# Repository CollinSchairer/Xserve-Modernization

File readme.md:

Making Apple's beautiful but whacky servers of old useable in 2023.

This project aims to adapt modern ATX computer hardware into the 1U Xserve chassis while maintaining as much of the original design and hardware as possible.
As I work through this project, less and less of this original hardware seems to be useable, but I'm trying my best.

The main components of this modification are a revised front panel I/O and indication board, hard drive caddy modifications, a revised and modernized 
SATA (Maybe SAS?) backplane, and a revised back panel to fit an ATX motherboard I/O cutout and Flex ATX power supply.
# Xserve-Modernization

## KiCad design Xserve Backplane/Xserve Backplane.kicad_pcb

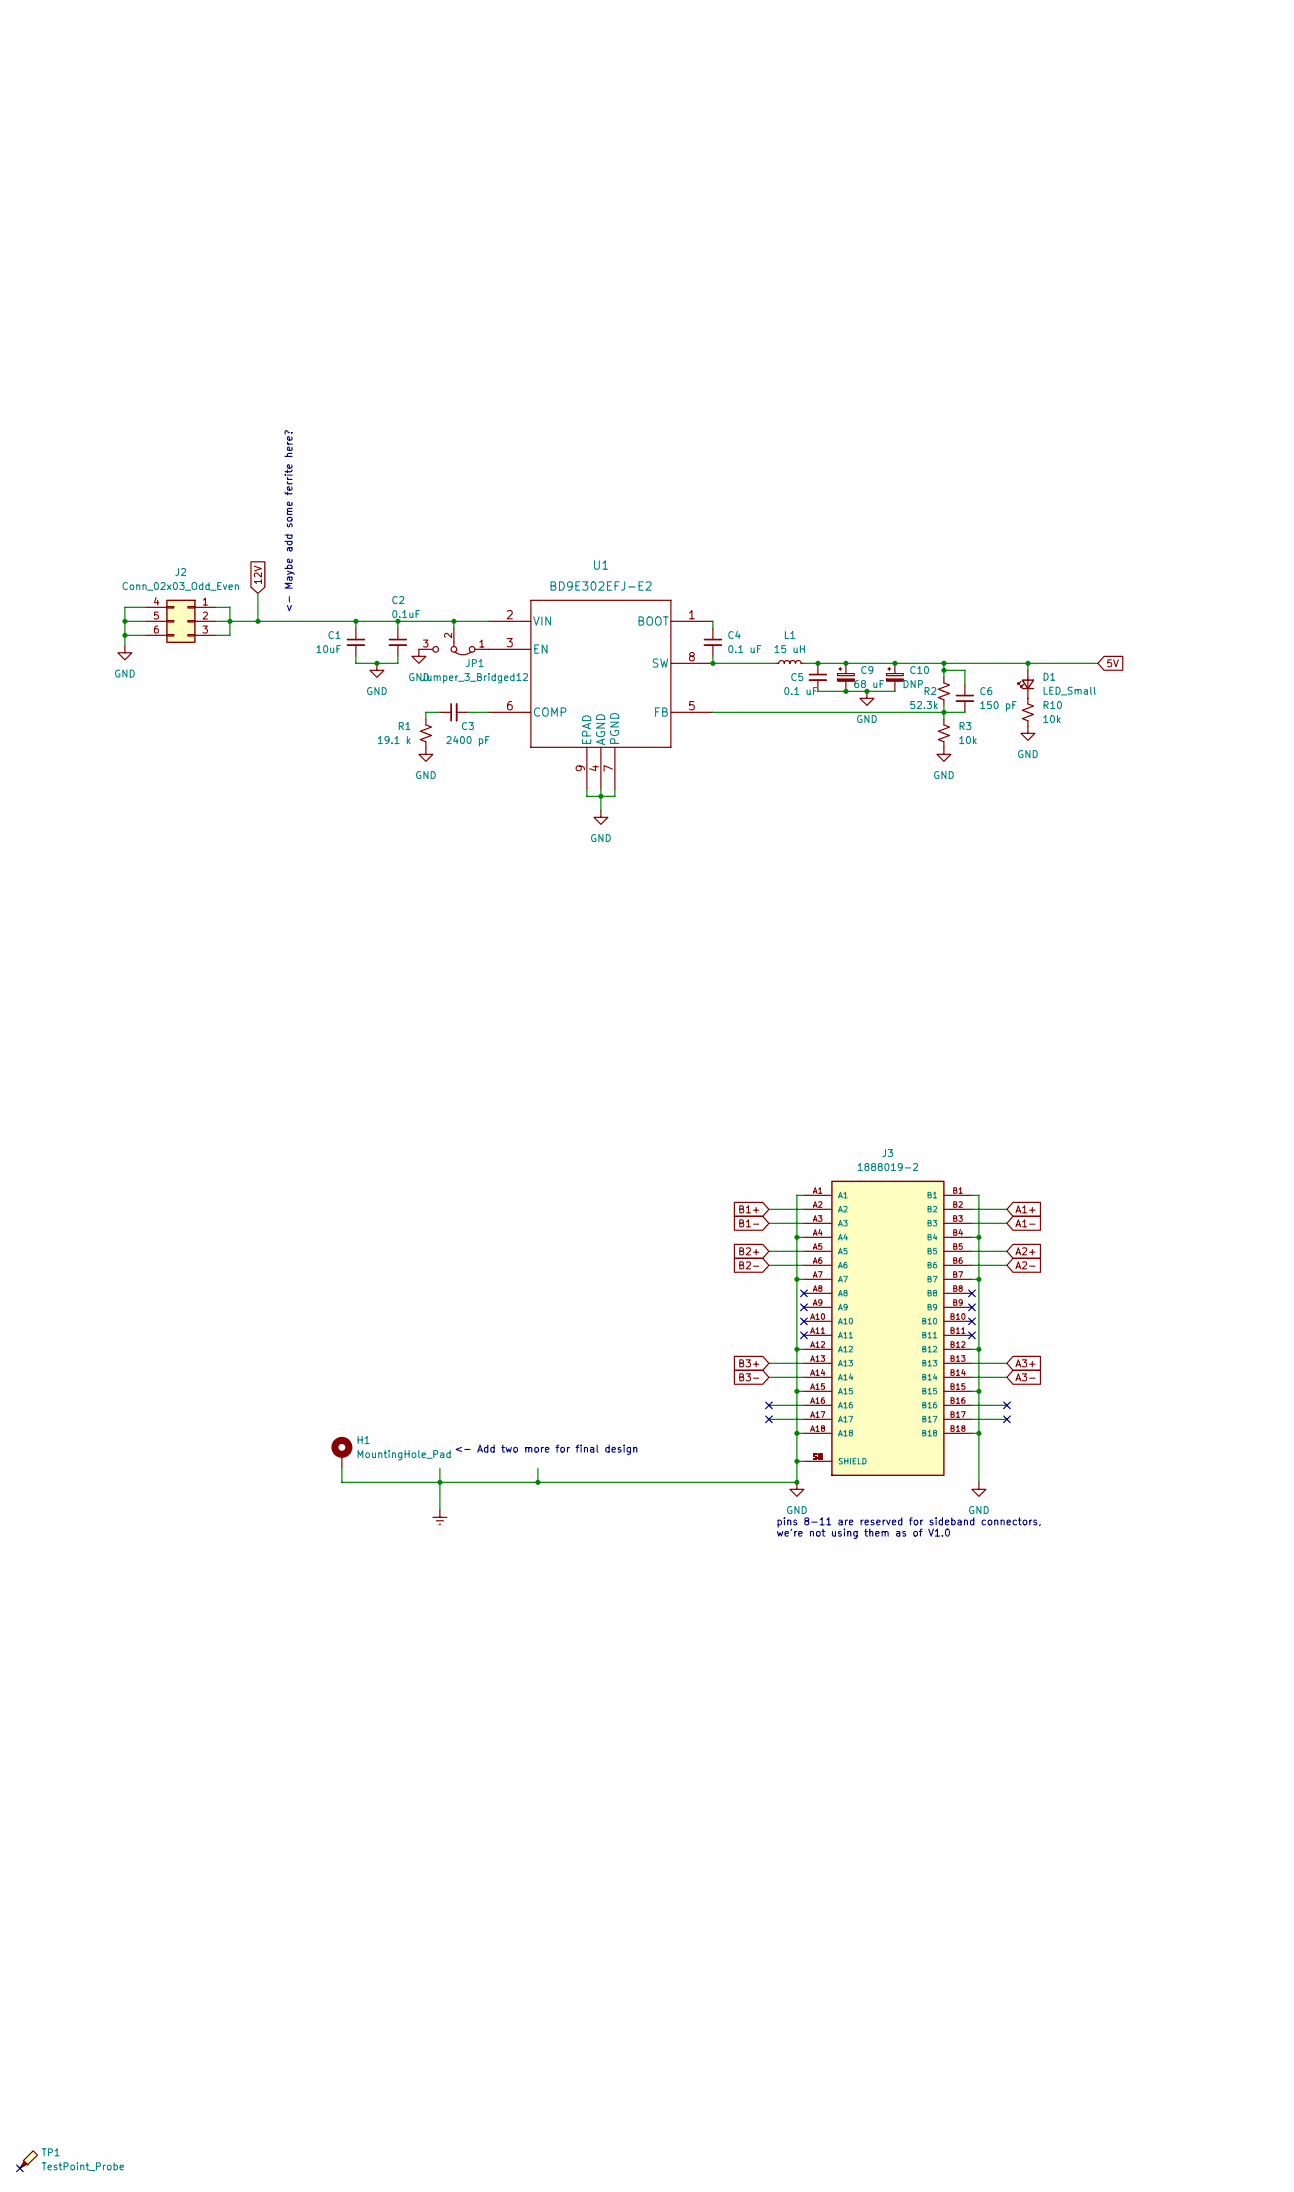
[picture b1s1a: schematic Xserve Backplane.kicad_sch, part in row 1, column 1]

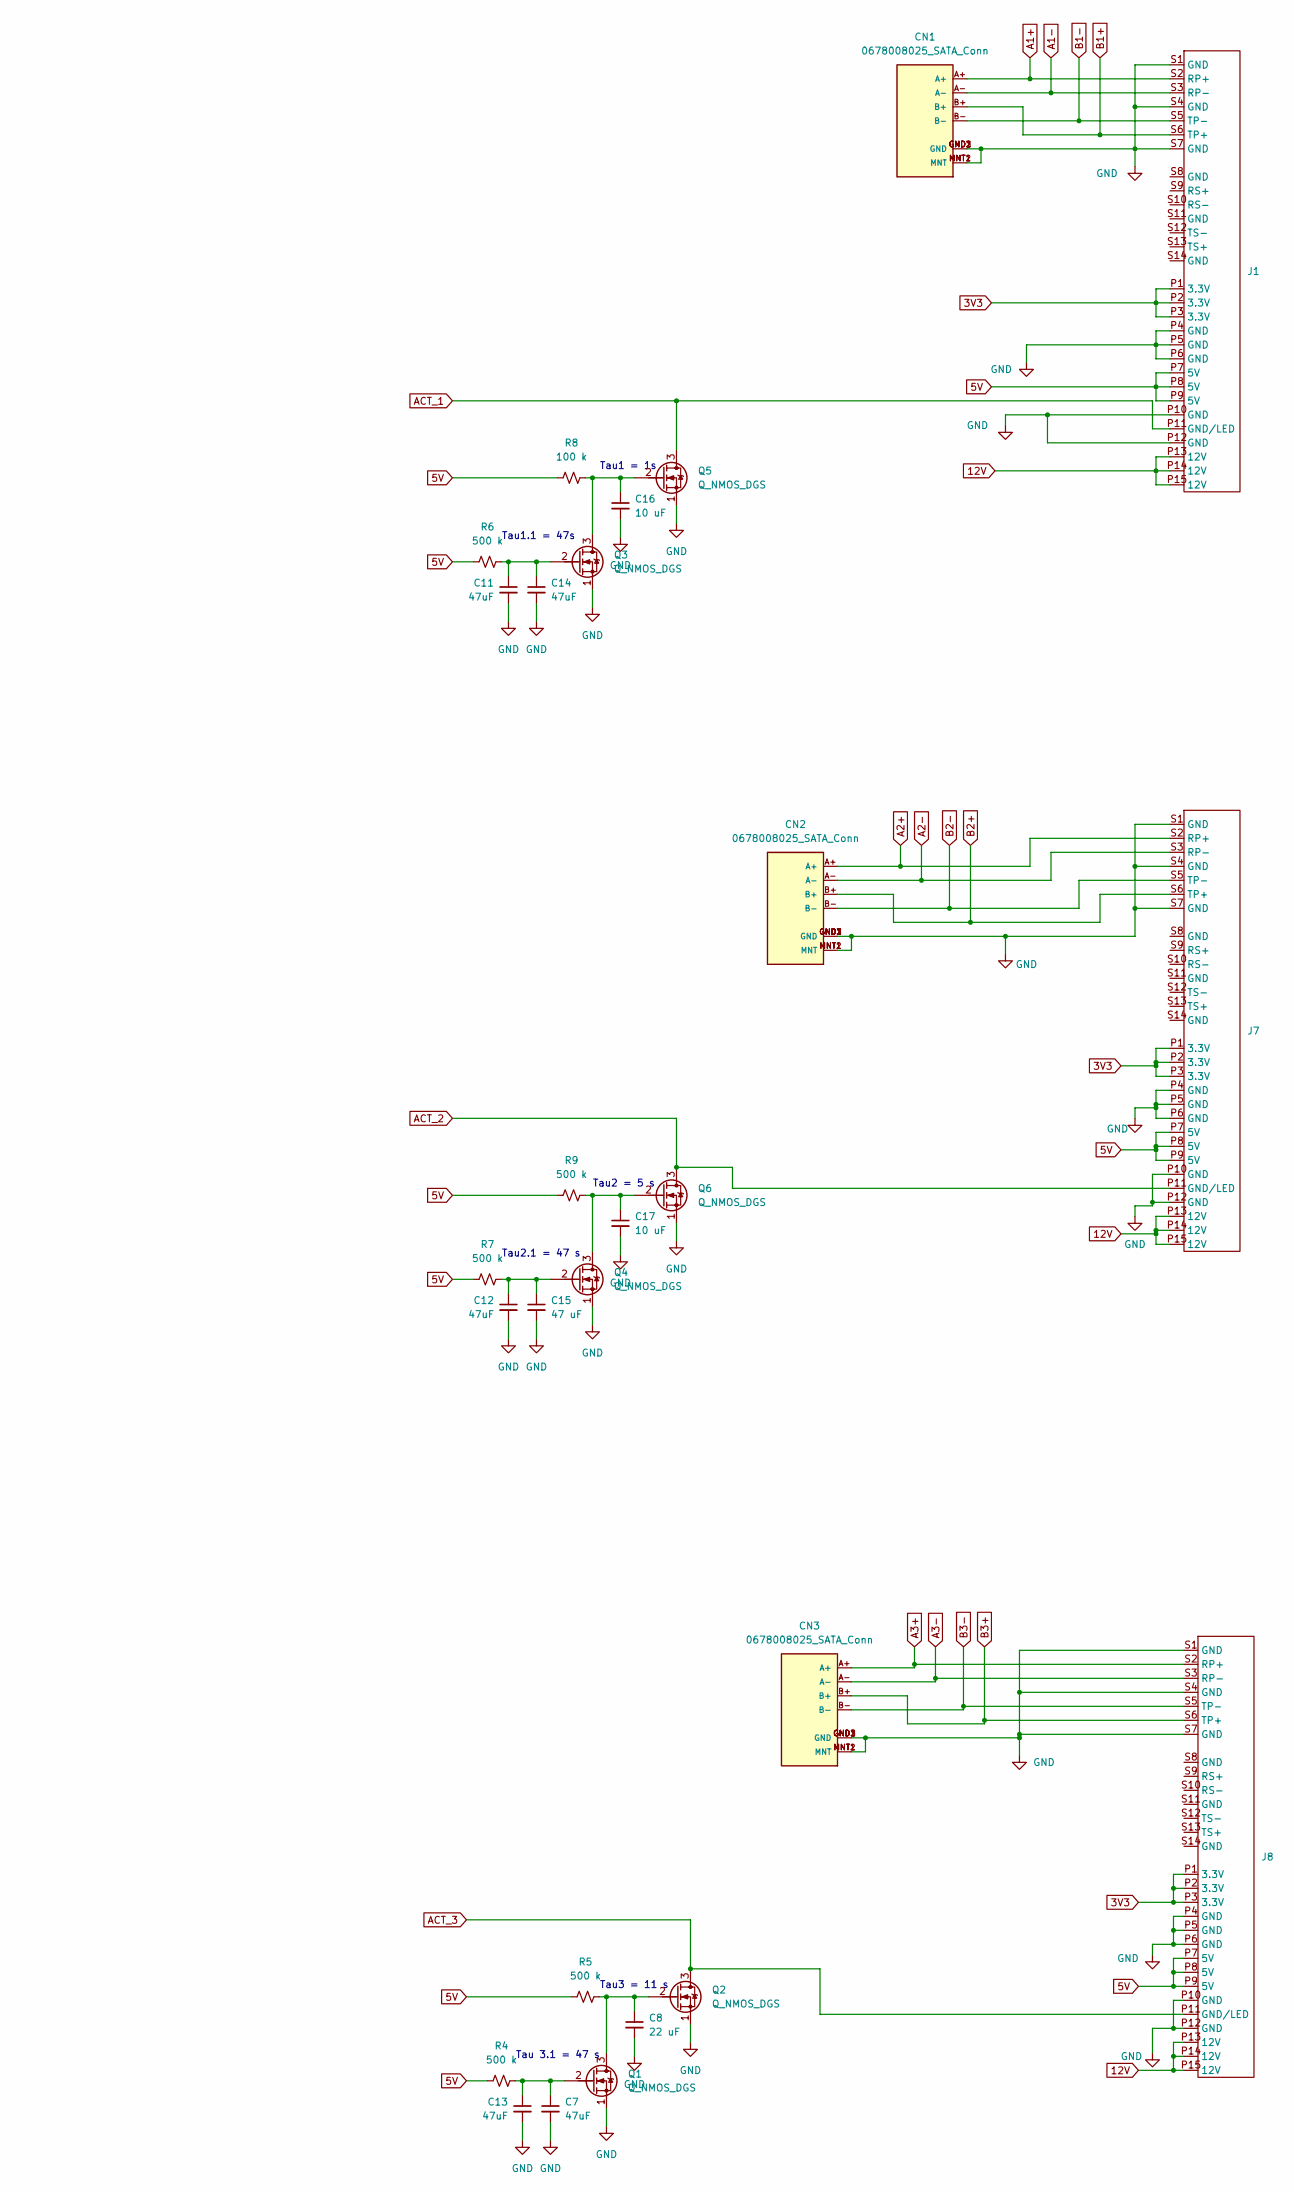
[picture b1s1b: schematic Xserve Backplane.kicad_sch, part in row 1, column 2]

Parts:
C1: 10uF; C_0603_1608Metric_Pad1.08x0.95mm_HandSolder
C2: 0.1uF; C_0603_1608Metric_Pad1.08x0.95mm_HandSolder
C3: 2400 pF; C_0603_1608Metric_Pad1.08x0.95mm_HandSolder
C4, C5: 0.1 uF; C_0603_1608Metric_Pad1.08x0.95mm_HandSolder
C6: 150 pF; C_0603_1608Metric_Pad1.08x0.95mm_HandSolder
C7, C11, C12, C13, C14: 47uF; C_1210_3225Metric_Pad1.33x2.70mm_HandSolder
C8: 22 uF; C_0603_1608Metric_Pad1.08x0.95mm_HandSolder
C9: 68 uF; CP_EIA-7343-15_Kemet-W_Pad2.25x2.55mm_HandSolder
C10: DNP; CP_EIA-7343-15_Kemet-W_Pad2.25x2.55mm_HandSolder
C15: 47 uF; C_1210_3225Metric_Pad1.33x2.70mm_HandSolder
C16, C17: 10 uF; C_0603_1608Metric_Pad1.08x0.95mm_HandSolder
CN1, CN2, CN3: 0678008025_SATA_Conn
D1: LED_Small; LED_0805_2012Metric_Pad1.15x1.40mm_HandSolder
H1: MountingHole_Pad; Slide Mount Hole
J1, J7, J8: 10124274-001TRLF
J2: Conn_02x03_Odd_Even; 6_pin_PCI_PWR
J3: 1888019-2; TE_1888019-2
JP1: Jumper_3_Bridged12; SolderJumper-3_P1.3mm_Bridged2Bar12_Pad1.0x1.5mm_NumberLabe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
L1: 15 uH; L_12x12mm_H8mm
Q1, Q2, Q3, Q4, Q5, Q6: Q_NMOS_DGS; SOT-23
R1: 19.1 k; R_0603_1608Metric_Pad0.98x0.95mm_HandSolder
R2: 52.3k; R_0603_1608Metric_Pad0.98x0.95mm_HandSolder
R3, R10: 10k; R_0603_1608Metric_Pad0.98x0.95mm_HandSolder
R4, R5, R6, R7, R9: 500 k; R_0603_1608Metric_Pad0.98x0.95mm_HandSolder
R8: 100 k; R_0603_1608Metric_Pad0.98x0.95mm_HandSolder
TP1: TestPoint_Probe; TheColonelCu
U1: BD9E302EFJ-E2; Texas_HTSOP-8-1EP_3.9x4.9mm_P1.27mm_EP2.95x4.9mm_Mask2.4x3.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

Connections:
3V3: J1.P1 (3.3V), J1.P2 (3.3V), J1.P3 (3.3V), J7.P1 (3.3V), J7.P2 (3.3V), J7.P3 (3.3V), J8.P1 (3.3V), J8.P2 (3.3V), J8.P3 (3.3V)
5V: C5.1, C6.1, C9.1, C10.1, D1.2 (A), J1.P7 (5V), J1.P8 (5V), J1.P9 (5V), J7.P7 (5V), J7.P8 (5V), J7.P9 (5V), J8.P7 (5V), J8.P8 (5V), J8.P9 (5V), L1.2, R2.1, R4.1, R5.1, R6.1, R7.1, R8.1, R9.1
12V: C1.1, C2.1, J1.P13 (12V), J1.P14 (12V), J1.P15 (12V), J2.1, J2.2, J2.3, J7.P13 (12V), J7.P14 (12V), J7.P15 (12V), J8.P13 (12V), J8.P14 (12V), J8.P15 (12V), JP1.2 (C), U1.2 (VIN)
A1+: CN1.A+, J1.S2 (RP+), J3.B2
A1-: CN1.A-, J1.S3 (RP-), J3.B3
A2+: CN2.A+, J3.B5, J7.S2 (RP+)
A2-: CN2.A-, J3.B6, J7.S3 (RP-)
A3+: CN3.A+, J3.B13, J8.S2 (RP+)
A3-: CN3.A-, J3.B14, J8.S3 (RP-)
ACT_1: J1.P11 (GND/LED), Q5.3 (D)
ACT_2: J7.P11 (GND/LED), Q6.3 (D)
ACT_3: J8.P11 (GND/LED), Q2.3 (D)
B1+: CN1.B+, J1.S6 (TP+), J3.A2
B1-: CN1.B-, J1.S5 (TP-), J3.A3
B2+: CN2.B+, J3.A5, J7.S6 (TP+)
B2-: CN2.B-, J3.A6, J7.S5 (TP-)
B3+: CN3.B+, J3.A13, J8.S6 (TP+)
B3-: CN3.B-, J3.A14, J8.S5 (TP-)
Earth: C1.2, C2.2, C5.2, C7.2, C8.2, C9.2, C10.2, C11.2, C12.2, C13.2, C14.2, C15.2, C16.2, C17.2, CN1.GND1 (GND), CN1.GND2 (GND), CN1.GND3 (GND), CN1.MNT1 (MNT), CN1.MNT2 (MNT), CN2.GND1 (GND), CN2.GND2 (GND), CN2.GND3 (GND), CN2.MNT1 (MNT), CN2.MNT2 (MNT), CN3.GND1 (GND), CN3.GND2 (GND), CN3.GND3 (GND), CN3.MNT1 (MNT), CN3.MNT2 (MNT), H1.1, J1.P4 (GND), J1.P5 (GND), J1.P6 (GND), J1.P10 (GND), J1.P12 (GND), J1.S1 (GND), J1.S4 (GND), J1.S7 (GND), J2.4, J2.5, J2.6, J3.A1, J3.A4, J3.A7, J3.A12, J3.A15, J3.A18, J3.B1, J3.B4, J3.B7, J3.B12, J3.B15, J3.B18, J3.S1 (SHIELD), J3.S2 (SHIELD), J3.S3 (SHIELD), J3.S4 (SHIELD), J3.S5 (SHIELD), J3.S6 (SHIELD), J7.P4 (GND), J7.P5 (GND), J7.P6 (GND), J7.P10 (GND), J7.P12 (GND), J7.S1 (GND), J7.S4 (GND), J7.S7 (GND), J8.P4 (GND), J8.P5 (GND), J8.P6 (GND), J8.P10 (GND), J8.P12 (GND), J8.S1 (GND), J8.S4 (GND), J8.S7 (GND), JP1.3 (B), Q1.1 (S), Q2.1 (S), Q3.1 (S), Q4.1 (S), Q5.1 (S), Q6.1 (S), R1.2, R3.2, R10.2, U1.4 (AGND), U1.7 (PGND), U1.9 (EPAD)
unnamed: C3.1, R1.1
unnamed: D1.1 (K), R10.1
unnamed: JP1.1 (A), U1.3 (EN)
unnamed: C8.1, Q1.3 (D), Q2.2 (G), R5.2
unnamed: C7.1, C13.1, Q1.2 (G), R4.2
unnamed: C16.1, Q3.3 (D), Q5.2 (G), R8.2
unnamed: C11.1, C14.1, Q3.2 (G), R6.2
unnamed: C17.1, Q4.3 (D), Q6.2 (G), R9.2
unnamed: C12.1, C15.1, Q4.2 (G), R7.2
unnamed: C4.1, U1.1 (BOOT)
unnamed: C3.2, U1.6 (COMP)
unnamed: C6.2, R2.2, R3.1, U1.5 (FB)
unnamed: C4.2, L1.1, U1.8 (SW)

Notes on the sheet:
Tau2.1 = 47 s
pins 8-11 are reserved for sideband connectors, we're not using them as of V1.0
<- Add two more for final design
Tau2 = 5 s
<- Maybe add some ferrite here?
Tau1 = 1s
Tau1.1 = 47s
Tau3 = 11 s
Tau 3.1 = 47 s

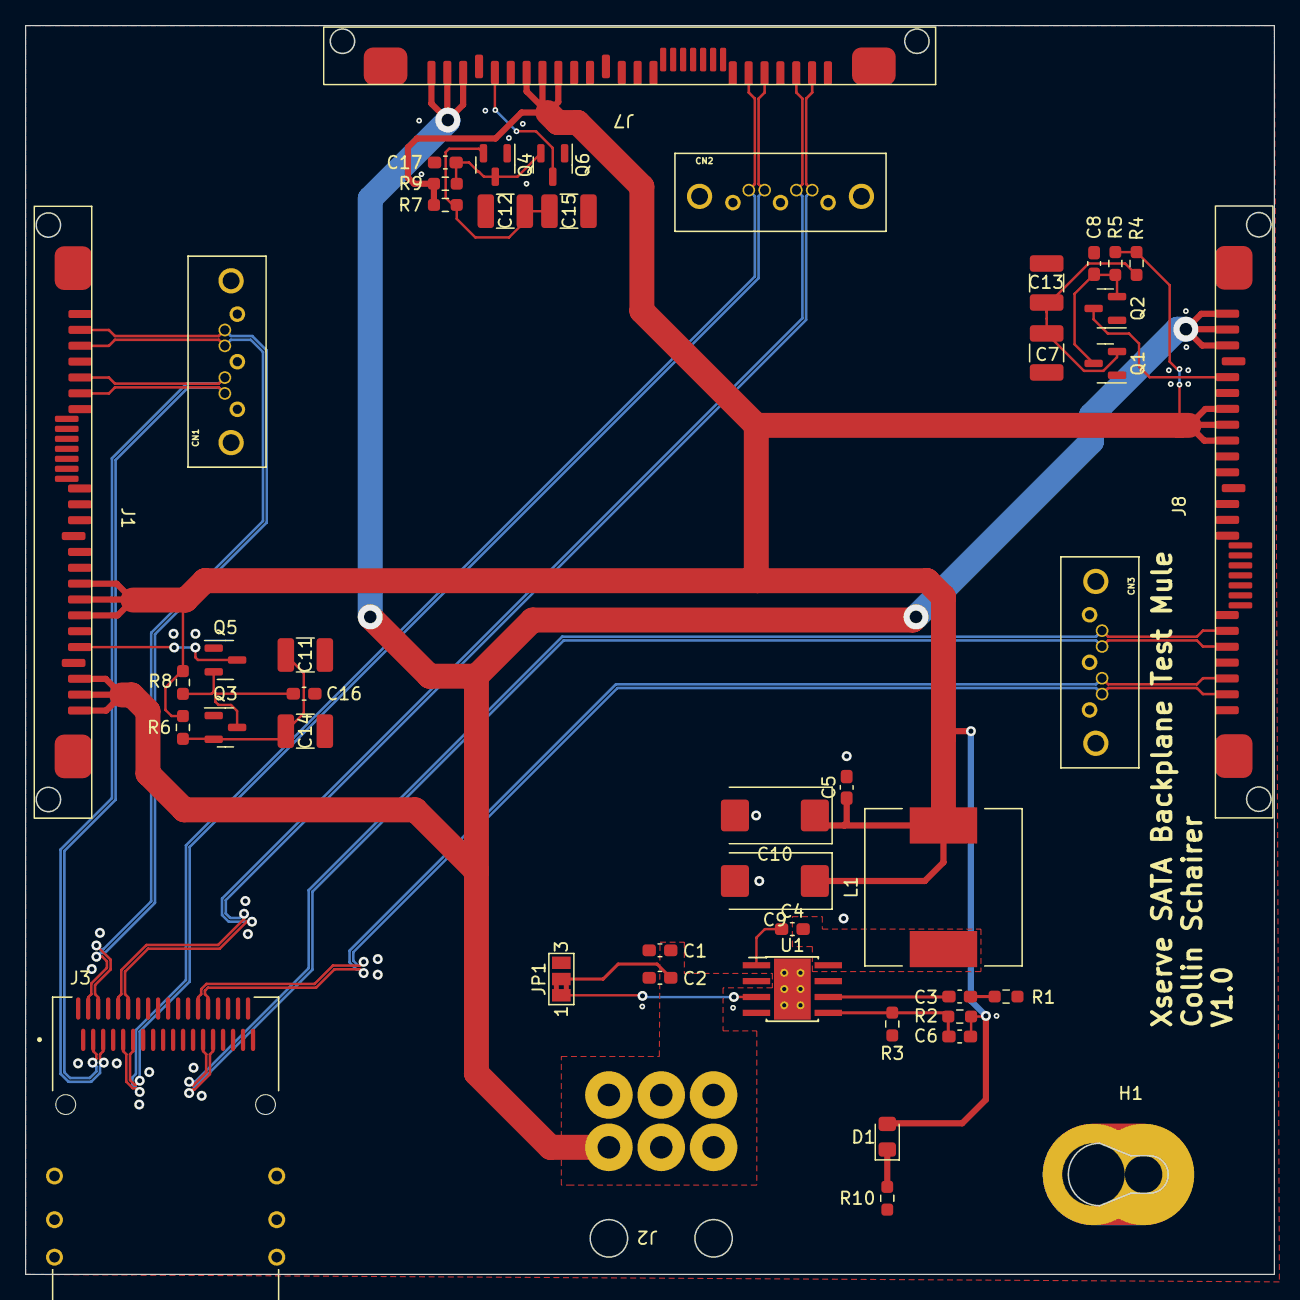
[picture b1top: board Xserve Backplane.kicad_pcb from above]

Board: 4 copper layers, 100.0 x 100.0 mm, 47 parts (0 on the bottom side), 32 nets.

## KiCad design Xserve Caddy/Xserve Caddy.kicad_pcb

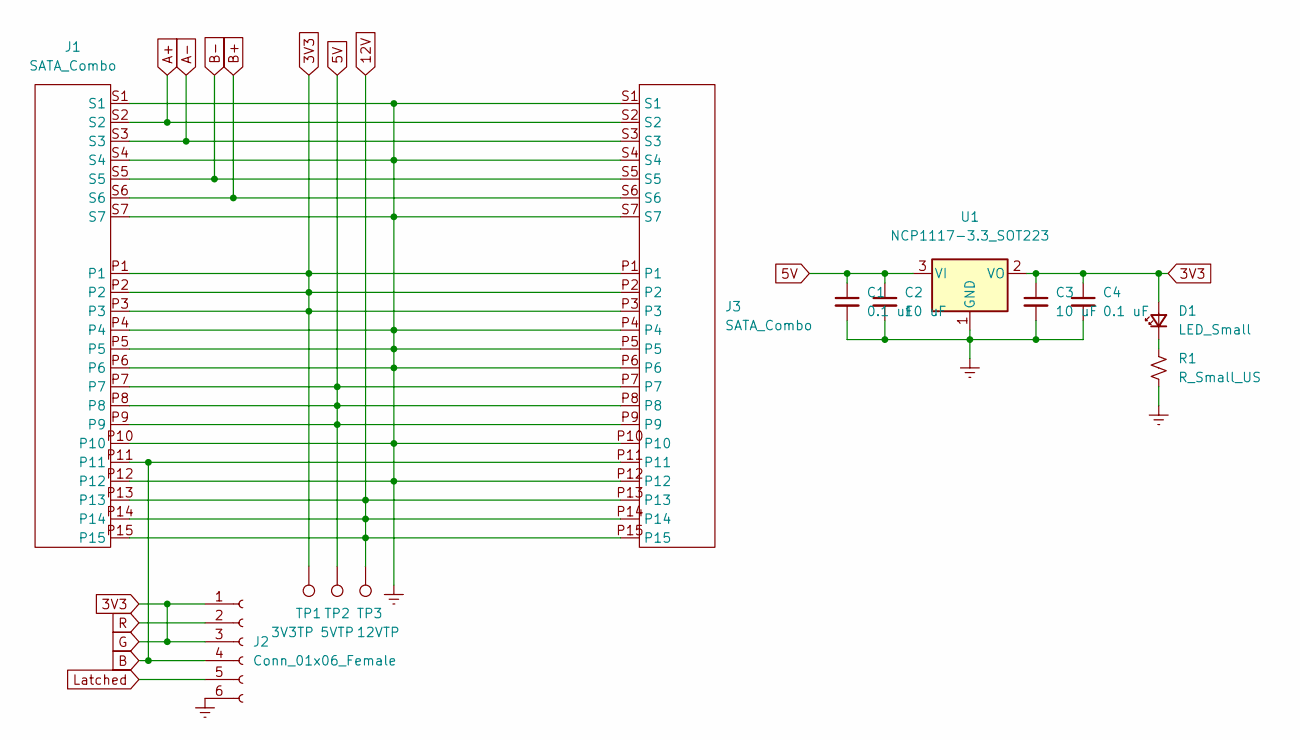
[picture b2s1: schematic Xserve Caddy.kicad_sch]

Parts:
C1, C4: 0.1 uF; C_0603_1608Metric_Pad1.08x0.95mm_HandSolder
C2, C3: 10 uF; C_0603_1608Metric_Pad1.08x0.95mm_HandSolder
D1: LED_Small; LED_0805_2012Metric_Pad1.15x1.40mm_HandSolder
J1, J3: SATA_Combo; 5622-2103-ML
J2: Conn_01x06_Female; Molex_PicoBlade_53048-0610_1x06_P1.25mm_Horizontal
R1: R_Small_US; R_0603_1608Metric_Pad0.98x0.95mm_HandSolder
TP1: 3V3TP; TestPoint_Pad_D2.0mm
TP2: 5VTP; TestPoint_Pad_D2.0mm
TP3: 12VTP; TestPoint_Pad_D2.0mm
U1: NCP1117-3.3_SOT223; SOT-223-3_TabPin2

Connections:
3V3: C3.1, C4.1, D1.2 (A), J1.P1, J1.P2, J1.P3, J2.1, J2.3, J3.P1, J3.P2, J3.P3, TP1.1, U1.2 (VO)
5V: C1.1, C2.1, J1.P7, J1.P8, J1.P9, J3.P7, J3.P8, J3.P9, TP2.1, U1.3 (VI)
12V: J1.P13, J1.P14, J1.P15, J3.P13, J3.P14, J3.P15, TP3.1
A+: J1.S2, J3.S2
A-: J1.S3, J3.S3
B: J1.P11, J2.4, J3.P11
B+: J1.S6, J3.S6
B-: J1.S5, J3.S5
Earth: C1.2, C2.2, C3.2, C4.2, J1.P4, J1.P5, J1.P6, J1.P10, J1.P12, J1.S1, J1.S4, J1.S7, J2.6, J3.P4, J3.P5, J3.P6, J3.P10, J3.P12, J3.S1, J3.S4, J3.S7, R1.2, U1.1 (GND)
Latched: J2.5
unnamed: D1.1 (K), R1.1
R: J2.2

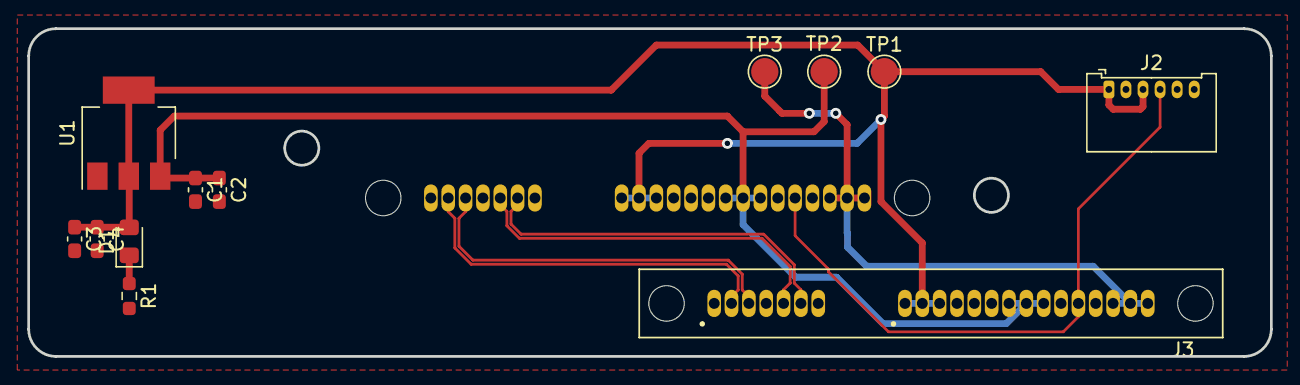
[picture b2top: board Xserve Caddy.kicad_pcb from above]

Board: 4 copper layers, 91.0 x 24.0 mm, 13 parts (1 on the bottom side), 10 nets.

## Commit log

2023-04-22 init project repo
2023-05-01 init of project on github
2023-05-01 init project on github
2023-05-26 "Ran DRC, changed mosfet footprint"
2023-06-15 small updates
2023-07-08 Creatd Ampehnol SAS connector footprint and implemented in schematic. Began implementation in layout.
2023-07-30 created SAS connector footprint and added to layout. next step is routing with new connector
2023-07-31 rough pass at SAS connector layout and some DRC fixes, this board should be manufacturable.
2023-11-16 misinterpreted JLC's via size capabilities. increased minimum via to 0.46 mm to comply with their requirements.
2023-11-28 got the front panel PCB schematic to a decent place. Just need to fill in the details (all the passive values, maybe add some fuses, clean up the schematic).
2024-02-05 Incremental changes, not exactly sure what's in this commit but thought it best to commit.
